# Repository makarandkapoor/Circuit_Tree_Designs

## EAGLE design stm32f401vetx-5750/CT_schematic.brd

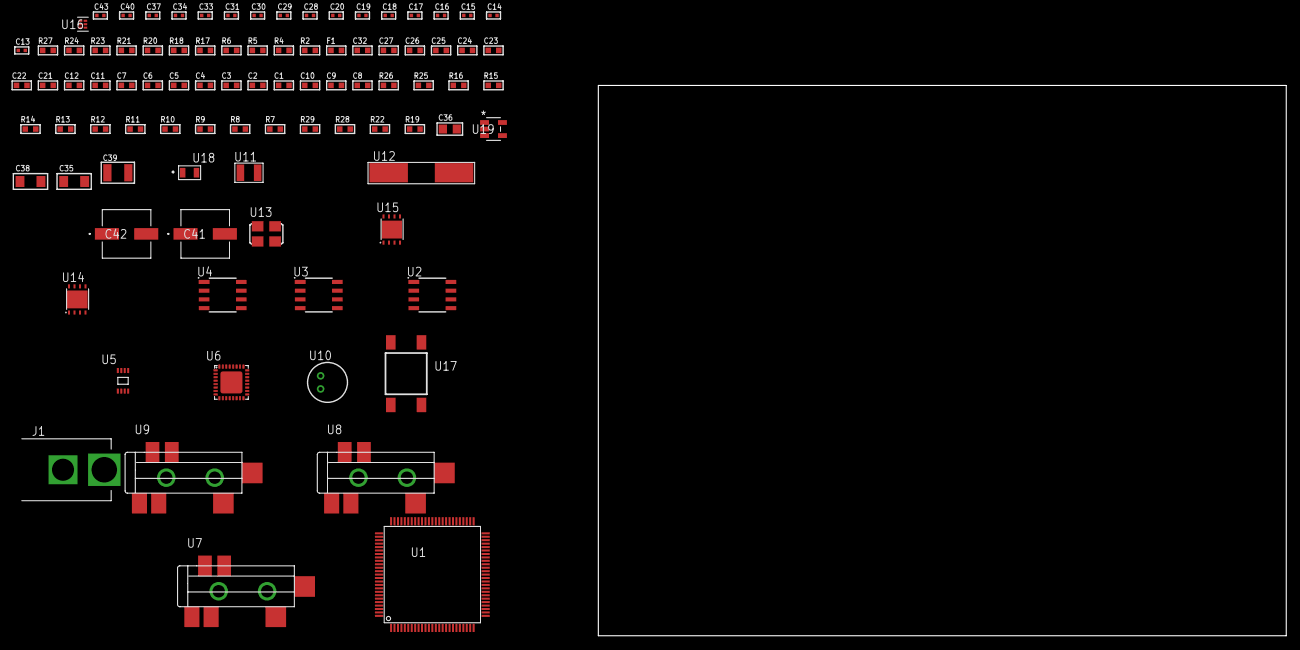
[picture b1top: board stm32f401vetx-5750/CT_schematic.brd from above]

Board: 2 copper layers, 100.0 x 80.0 mm, 91 parts (0 on the bottom side), 62 nets, no tracks yet.

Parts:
C1, C12, C21, C22, C23, C24, C25, C26, C27, C32: 1e-06; C0603
C2, C3, C4, C5, C6, C7: 1e-07; C0603
C8: 4.7e-06; C0603
C9, C10: 2.2e-06; C0603
C11: 1e-08; C0603
C13, C14, C15, C16: 1e-11; C0402
C17, C18, C19, C20, C33, C34, C37, C43: 1e-08; C0402
C28, C29, C30, C31, C40: 1e-07; C0402
C35, C38: 1e-05; C1206
C36: 1e-05; C0805
C39: 1e-05; C1210
C41, C42: 0.0001; EXV-9H
F1: 240.0; L0603
J1: PJ-037B; PJ-037B_PACKAGE
R2, R21, R24: 1000.0; R0603
R4: 4700.0; R0603
R5, R6: 2200.0; R0603
R7, R8, R9, R10, R11, R12, R13, R14, R15, R16, R25, R26: 10000.0; R0603
R17, R18: 1270.0; R0603
R19, R22: 100000.0; R0603
R20: 200.0; R0603
R23: 2231.0; R0603
R27: 9100.0; R0603
R28: 680000.0; R0603
R29: 120000.0; R0603
U1: STM32F401VET6; LQFP100
U2: AT25010B-SSHL-T; SOIC-8
U3: AT25128B-SSHL-T; SOIC-8
U4: AT25512N-SH-T; SOIC-8
U5: 24AA01T-I/MNY; TDFN-8/6MM
U6: SGTL5000XNAA3; QFN-32
U7, U8, U9: SJ-43515TS-SMT-TR
U10: WM-64PCT; WM-64PC
U11: ABS07-32.768KHZ-7-T
U12: ABLS-25.000MHZ-B2F-T
U13: ASFL-24.57MHZ-NCS; ASFL1
U14, U15: LP3878SDX-ADJ/NOPB; WSON-8
U16: TPS3895ADRYR; SON-6
U17: 4-1437565-2; SW_4-1437565-2
U18: Q65110A2395; LGM67K-G1J2-24-Z
U19: nc7sz125m5x; NC7SZ125M5X

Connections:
CLK_CRYSTAL_U1_8: C13.1, U1.8, U11.1
CLK_CRYSTAL_U1_9: C14.1, U1.9, U11.2
CLK_CRYSTAL_U1_12: C15.1, U1.12, U12.1
CLK_CRYSTAL_U1_13: C16.1, U1.13, U12.2
CLK_U6_21: U6.21, U13.3
GND: C1.2, C2.2, C3.2, C4.2, C5.2, C6.2, C7.2, C8.2, C9.2, C10.2, C11.2, C12.2, C13.2, C14.2, C15.2, C16.2, C17.2, C18.2, C19.2, C20.2, C28.2, C29.2, C30.2, C31.2, C32.2, C33.2, C34.2, C35.2, C36.2, C37.2, C38.2, C39.2, C40.2, C41.2, C42.2, C43.2, J1.2, R2.2, R7.2, R18.2, R21.2, R24.2, R27.2, R29.2, U1.10, U1.20, U1.27, U1.49, U1.74, U1.99, U2.4, U3.4, U4.4, U5.4, U5.7, U6.1, U6.3, U6.7, U6.EXP, U8.1, U9.1, U10.2, U13.2, U14.3, U14.PAD, U15.3, U15.PAD, U16.2, U18.C, U19.1, U19.3
NET_U1_14: R4.1, U1.14, U19.4
NET_U1_22: C11.1, C12.1, F1.1, U1.21, U1.22
NET_U1_48: C9.1, U1.48
NET_U1_73: C10.1, U1.73
NET_U1_92: R5.1, U1.92, U5.6
NET_U1_93: R6.1, U1.93, U5.5
NET_U1_94: R7.1, U1.94
NET_U1_98: U17.3, U17.4
NET_U2_3: R8.1, U2.3
NET_U2_7: R10.1, U2.7
NET_U3_3: R11.1, U3.3
NET_U3_7: R13.1, U3.7
NET_U4_3: R14.1, U4.3
NET_U4_7: R16.1, U4.7
NET_U6_10: C31.1, U6.10
NET_U6_29: R17.1, U6.29
NET_U6_31: R18.1, U6.31
NET_U7_1: U6.4, U7.1
NET_U7_2: U6.2, U7.2
NET_U7_5: U6.6, U7.5
NET_U8_2: C22.1, U8.2
NET_U8_5: C21.1, U8.5
NET_U9_2: C24.1, C25.1, U9.2
NET_U9_5: C23.1, U9.5
NET_U9_13: C24.2, C25.2
NET_U10_1: C26.1, C27.1, C32.1, U6.16, U10.1
NET_U10_15: C26.2, C27.2
NET_U14_1: C34.1, U14.1
NET_U14_6: R20.2, R21.1, U14.6
NET_U14_8: R19.1, U14.8
NET_U15_1: C37.1, U15.1
NET_U15_6: R23.2, R24.1, U15.6
NET_U15_8: R22.1, U15.8
NET_U16_1: R26.1, R27.1, U16.1
NET_U16_3: R28.2, R29.1, U16.3
NET_U16_4: R25.1, U16.4, U19.2
NET_U17_1: R2.1, U17.1, U17.2
PROC_I2S2_CK: U1.52, U6.24
PROC_I2S2_EXT_SD: U1.53, U6.25
PROC_I2S2_SD: U1.54, U6.26
PROC_I2S2_WS: U1.96, U6.23
PROC_SPI1_MISO: U1.31, U4.2
PROC_SPI1_MOSI: U1.32, U4.5
PROC_SPI1_NSS: R15.1, U1.29, U4.1
PROC_SPI1_SCK: U1.30, U4.6
PROC_SPI2_MISO: U1.17, U2.2
PROC_SPI2_MOSI: U1.18, U2.5
PROC_SPI2_NSS: R9.1, U1.51, U2.1
PROC_SPI2_SCK: U1.47, U2.6
PROC_SPI3_MISO: U1.79, U3.2
PROC_SPI3_MOSI: U1.80, U3.5
PROC_SPI3_NSS: R12.1, U1.77, U3.1
PROC_SPI3_SCK: U1.78, U3.6
VCC_S1_7V1: C35.1, C38.1, C41.1, C42.1, J1.1, R19.2, R22.2, U14.4, U15.4
VCC_TIER1_1V2: C28.1, C36.1, R20.1, U6.30, U14.5
VCC_TIER1_3V3: C1.1, C2.1, C3.1, C4.1, C5.1, C6.1, C7.1, C8.1, C17.1, C18.1, C19.1, C20.1, C29.1, C30.1, C33.1, C39.1, C40.1, C43.1, F1.2, R4.2, R5.2, R6.2, R8.2, R9.2, R10.2, R11.2, R12.2, R13.2, R14.2, R15.2, R16.2, R17.2, R23.1, R25.2, R26.2, R28.1, U1.6, U1.11, U1.19, U1.28, U1.50, U1.75, U1.100, U2.8, U3.8, U4.8, U5.8, U6.5, U6.20, U13.4, U15.5, U16.6, U19.5

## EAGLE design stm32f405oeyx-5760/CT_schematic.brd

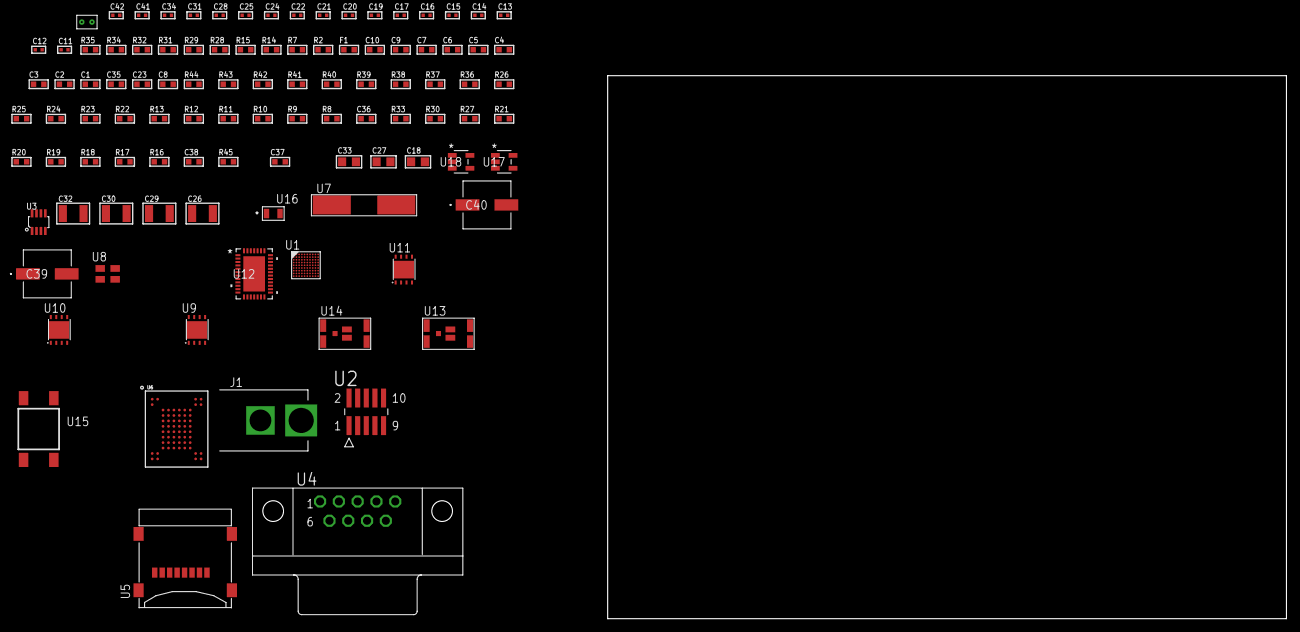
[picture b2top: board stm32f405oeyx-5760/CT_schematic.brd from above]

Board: 2 copper layers, 100.0 x 80.0 mm, 103 parts (0 on the bottom side), 71 nets, no tracks yet.

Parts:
C1, C10: 1e-06; C0603
C2, C3, C4, C5, C6, C7: 1e-07; C0603
C8: 4.7e-06; C0603
C9: 1e-08; C0603
C11, C12, C15, C16, C17, C19, C20, C21, C22, C34: 1e-07; C0402
C13, C14: 1e-11; C0402
C18, C27, C33: 1e-05; C0805
C23, C35: 2.2e-06; C0603
C24, C25, C28, C31, C41, C42: 1e-08; C0402
C26, C29, C30, C32: 1e-05; C1210
C36: 2.45e-08; R0603
C37: 2.8258362168397e-09; R0603
C38: 7.105e-09; R0603
C39, C40: 0.0001; EXV-9H
F1: 240.0; L0603
J1: PJ-037B; PJ-037B_PACKAGE
R2, R29, R32, R35: 1000.0; R0603
R7: 4700.0; R0603
R8, R9, R10, R11, R12, R13, R22, R23, R24, R25, R26, R36, R38, R39, R42, R43, R44: 10000.0; R0603
R14: 5.0; R0603
R15: 120.0; R0603
R16, R17, R18, R19, R20, R21, R27, R30, R33: 100000.0; R0603
R28, R34: 200.0; R0603
R31: 2231.0; R0603
R37: 75000.0; R0603
R40, R41: 95300.0; R0603
R45: 103345.45454545; R0603
U1: STM32F405OEY6; WLCSP90
U2: FTSH-105-01-L-DV-K; SAMTEC_FTSH-105-01-L-DV-K
U3: MAX3051EKA+T; SOT-23-8
U4: 182-009-113R531; 182-009-MALE
U5: 0472192001; MOLEX_47219-2001
U6: mt29f4g08abadah4; VFBGA-63
U7: ABLS-25.000MHZ-B2F-T
U8: ASEK-32.768KHz-ECST; ASEK
U9, U10, U11: LP3878SDX-ADJ/NOPB; WSON-8
U12: LTC2928CUHF#PBF; QFN-38_UHF
U13, U14: IRF8306MTRPbF; IRF8306MTRPBF
U15: 4-1437565-2; SW_4-1437565-2
U16: Q65110A2395; LGM67K-G1J2-24-Z
U17, U18: nc7sz125m5x; NC7SZ125M5X
U19: Dummy; DUMMY_PACKAGE_230

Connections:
CLK_CRYSTAL_U1_F9: C13.1, U1.F9, U7.1
CLK_CRYSTAL_U1_F10: C14.1, U1.F10, U7.2
CLK_U1_B10: U1.B10, U8.3
GND: C1.2, C2.2, C3.2, C4.2, C5.2, C6.2, C7.2, C8.2, C9.2, C10.2, C11.2, C12.2, C13.2, C14.2, C15.2, C16.2, C17.2, C18.2, C19.2, C20.2, C21.2, C22.2, C23.2, C24.2, C25.2, C26.2, C27.2, C28.2, C29.2, C30.2, C31.2, C32.2, C33.2, C34.2, C35.2, C36.2, C37.2, C38.2, C39.2, C40.2, C41.2, C42.2, J1.2, R2.2, R9.2, R14.2, R29.2, R32.2, R35.2, R37.2, R40.2, R41.2, R42.2, R43.2, R44.2, U1.C9, U1.E5, U1.E7, U1.E8, U1.H10, U2.3, U2.5, U3.2, U3.8, U4.5, U5.6, U5.G1, U5.G2, U5.G3, U5.G4, U6.C5, U6.F7, U6.K3, U6.K8, U8.2, U9.3, U9.PAD, U10.3, U10.PAD, U11.3, U11.PAD, U12.8, U12.9, U12.10, U12.12, U12.13, U12.24, U12.25, U12.30, U12.32, U12.39, U16.C, U17.2, U17.3, U18.1, U18.3, U19.1
NET_U1_A7: R9.1, U1.A7
NET_U1_A8: R8.1, U1.A8
NET_U1_B1: C12.1, U1.B1
NET_U1_D9: R10.1, U1.D9
NET_U1_G9: C9.1, C10.1, F1.1, U1.G9
NET_U1_G10: R7.1, U1.G10, U18.4
NET_U1_J10: U15.3, U15.4
NET_U2_9: R14.1, U2.9
NET_U3_6: R15.2, U3.6
NET_U4_2: R15.2, U3.6, U4.2
NET_U4_3: R15.1, U3.7, U4.3
NET_U6_C3: R26.1, U6.C3
NET_U9_1: C25.1, U9.1
NET_U9_6: R28.2, R29.1, U9.6
NET_U9_8: R27.1, U9.8
NET_U10_1: C28.1, U10.1
NET_U10_6: R31.2, R32.1, U10.6
NET_U10_8: R30.1, U10.8
NET_U11_1: C31.1, U11.1
NET_U11_6: R34.2, R35.1, U11.6
NET_U11_8: R33.1, U11.8
NET_U12_3: R43.1, U12.3
NET_U12_6: R40.1, U12.6
NET_U12_7: R41.1, U12.7
NET_U12_16: R42.1, R45.1, U12.16
NET_U12_18: R39.1, U12.18
NET_U12_19: R38.1, U12.19, U12.20
NET_U12_21: R36.1, R37.1, U12.21, U17.4, U18.2
NET_U12_22: C34.1, R36.2, R38.2, R39.2, U12.11, U12.22
NET_U12_26: C37.1, U12.26
NET_U12_27: C36.1, U12.27
NET_U12_28: C38.1, U12.28
NET_U12_38: R44.1, U12.38
NET_U13_3: U12.2, U13.3
NET_U14_3: U12.37, U14.3
NET_U15_1: R2.1, U15.1, U15.2
PROC_CAN1_RX: U1.C1, U3.4
PROC_CAN1_TX: U1.C2, U3.1
PROC_DAC_OUT2: U1.G8, U19.2
PROC_FSMC_D0: U1.F2, U6.H4
PROC_FSMC_D1: U1.F1, U6.J4
PROC_FSMC_D2: U1.D6, U6.K4
PROC_FSMC_D3: U1.C5, U6.K5
PROC_FSMC_D4: U1.G6, U6.K6
PROC_FSMC_D5: U1.H6, U6.J7
PROC_FSMC_D6: U1.J6, U6.K7
PROC_FSMC_D7: U1.F6, U6.J8
PROC_FSMC_NCE2: R23.1, U1.A5, U6.C6
PROC_FSMC_NOE: R25.1, U1.A4, U6.D4
PROC_FSMC_NWAIT: R22.1, U1.B5, U6.C8
PROC_FSMC_NWE: R24.1, U1.C6, U6.C7
PROC_SDIO_CK: R17.1, U1.A3, U5.5
PROC_SDIO_CMD: R16.1, U1.B4, U5.3
PROC_SDIO_D0: R18.1, U1.E2, U5.7
PROC_SDIO_D1: R19.1, U1.E3, U5.8
PROC_SDIO_D2: R20.1, U1.D5, U5.1
PROC_SDIO_D3: R21.1, U1.C4, U5.2
PROC_SYS_JTCK_SWCLK: R12.1, U1.A2, U2.4
PROC_SYS_JTDO_SWO: U1.B6, U2.6
PROC_SYS_JTMS_SWDIO: R13.1, U1.D4, U2.2
RST_OUT_U2_JTAG_RST_B: R11.1, U2.10, U17.1
VCC_12V7: C35.1, C39.1, C40.1, J1.1, R45.2, U12.23, U13.1, U13.2, U13.6, U13.7, U14.1, U14.2, U14.6, U14.7
VCC_S1_12V7: C26.1, C29.1, R27.2, R30.2, U9.4, U10.4, U13.4, U13.5
VCC_S2_12V7: C32.1, R33.2, U11.4, U14.4, U14.5
VCC_TIER1_1V2: C11.1, C27.1, R28.1, U1.F4, U9.5
VCC_TIER1_3V3: C1.1, C2.1, C3.1, C4.1, C5.1, C6.1, C7.1, C8.1, C15.1, C16.1, C17.1, C18.1, C19.1, C20.1, C21.1, C22.1, C23.1, C24.1, C30.1, C41.1, C42.1, F1.2, R7.2, R8.2, R10.2, R11.2, R12.2, R13.2, R16.2, R17.2, R18.2, R19.2, R20.2, R21.2, R22.2, R23.2, R24.2, R25.2, R26.2, R31.1, U1.A1, U1.A10, U1.B8, U1.E4, U1.E6, U1.F7, U2.1, U3.3, U5.4, U6.D3, U6.G4, U6.H8, U6.J6, U8.4, U10.5, U17.5, U18.5
VCC_TIER2_1V2: C33.1, R34.1, U11.5

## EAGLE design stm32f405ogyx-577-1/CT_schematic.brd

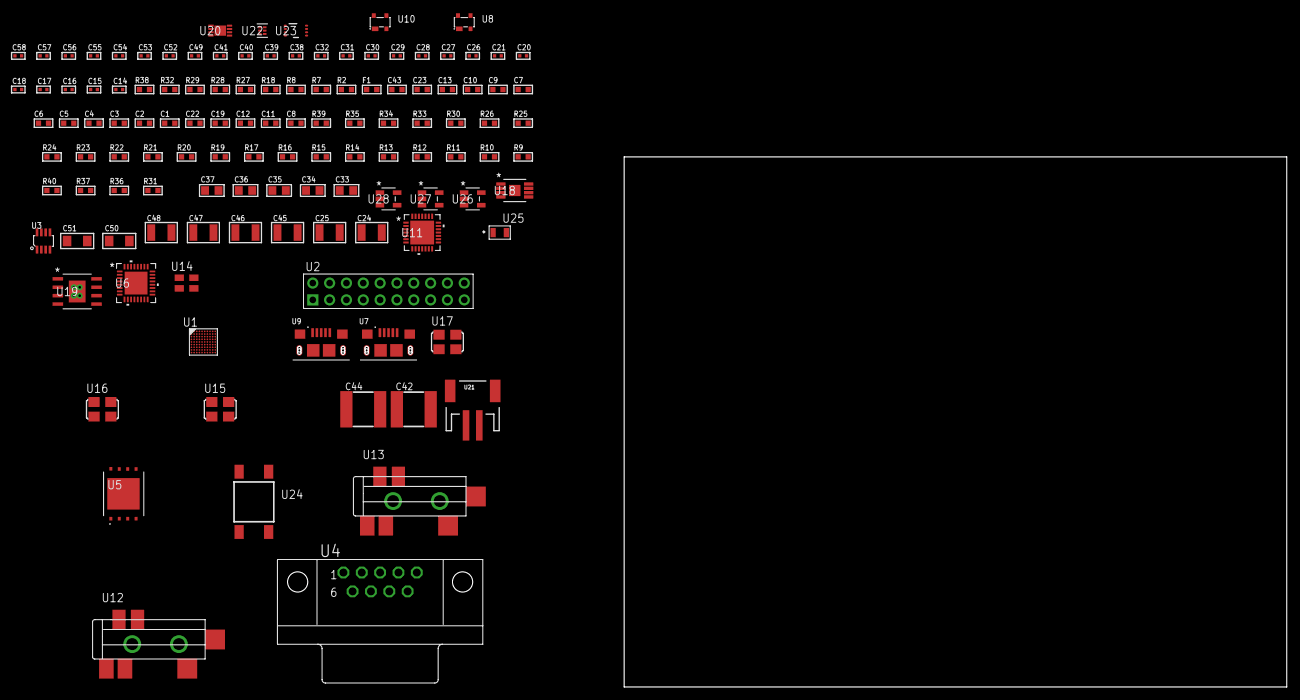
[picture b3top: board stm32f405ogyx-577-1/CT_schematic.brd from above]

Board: 2 copper layers, 122 parts (0 on the bottom side), 74 nets, no tracks yet.

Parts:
C1, C10, C13, C23, C43: 1e-06; C0603
C2, C3, C4, C5, C6, C7: 1e-07; C0603
C8: 4.7e-06; C0603
C9: 1e-08; C0603
C11, C12, C19, C22: 2.2e-06; C0603
C14, C15, C16, C18, C20, C21, C28, C29, C30, C31, C32, C49, C53, C55: 1e-07; C0402
C17, C38, C39, C40, C41, C52, C54, C56, C57, C58: 1e-08; C0402
C24, C25: 2.2e-05; C1210
C26, C27: 1e-09; C0402
C33, C34, C35, C36, C37: 1e-05; C0805
C42, C44: 6.8e-05; 2220
C45, C46, C47, C48: 1e-05; C1210
C50, C51: 1e-05; C1206
F1: 240.0; L0603
R2: 1000.0; R0603
R7, R8: 4700.0; R0603
R9, R10, R11, R12, R13, R14, R15, R16, R17, R19, R20, R21, R22, R23, R30, R33, R34, R39: 10000.0; R0603
R18: 120.0; R0603
R24, R25, R26: 47000.0; R0603
R27: 680.0; R0603
R28: 3900.0; R0603
R29, R32: 2200.0; R0603
R31: 4031.5447154472; R0603
R35: 82000.0; R0603
R36: 300000.0; R0603
R37: 120000.0; R0603
R38: 2000.0; R0603
R40: 200000.0; R0603
U1: STM32F405OGY6; WLCSP90
U2: TST-110-05-T-D-RA
U3: MAX3051EKA+T; SOT-23-8
U4: 182-009-113R531; 182-009-MALE
U5: S25FL128SDPNFI001; WNG008
U6: TUSB1210BRHBR; RHB32_3P45X3P45
U7, U9: 10118193-0001LF; FCI_10118193-0001LF
U8, U10: prtr5v0u2ax; SOT143B
U11: WM8731CLSEFL; QFN-28
U12, U13: SJ-43515TS-SMT-TR
U14: ASEK-32.768KHz-ECST; ASEK
U15: ASFL1-12.288MHZ-EC-T; ASFL1
U16: ASFL1-19.2MHZ-NCS; ASFL1
U17: ASFL1-25MHZ-NCS; ASFL1
U18: MIC47100YMME; MSOP-8_EP
U19: MIC5234YME; SOIC-8_EP
U20: MCP73831T-2ACI/MC; DFN8_2X3MC
U21: S2B-PH-SM4-TB(LF)(SN); JST-2-SMD
U22: TPS3895ADRYR; SON-6
U23: LSF0102DCTR; DCU0008A_N
U24: 4-1437565-2; SW_4-1437565-2
U25: Q65110A2395; LGM67K-G1J2-24-Z
U26, U27, U28: nc7sz125m5x; NC7SZ125M5X

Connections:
CLK_U1_B10: U1.B10, U14.3
CLK_U1_F10: U1.F10, U17.3
CLK_U6_1: U6.1, U16.3
CLK_U11_1: U11.1, U15.3
GND: C1.2, C2.2, C3.2, C4.2, C5.2, C6.2, C7.2, C8.2, C9.2, C10.2, C11.2, C12.2, C13.2, C14.2, C15.2, C16.2, C17.2, C18.2, C19.2, C20.2, C21.2, C22.2, C23.2, C27.2, C28.2, C29.2, C30.2, C31.2, C32.2, C33.2, C34.2, C35.2, C36.2, C37.2, C38.2, C39.2, C40.2, C41.2, C42.2, C43.2, C44.2, C45.2, C46.2, C47.2, C48.2, C49.2, C50.2, C51.2, C52.2, C53.2, C54.2, C55.2, C56.2, C57.2, C58.2, R2.2, R10.2, R11.2, R17.2, R23.2, R24.2, R25.2, R26.2, R29.2, R32.2, R35.2, R37.2, R38.2, U1.C1, U1.C9, U1.E5, U1.E7, U1.E8, U1.H10, U2.4, U2.6, U2.8, U2.10, U2.12, U2.14, U2.16, U2.18, U2.20, U3.2, U3.8, U4.5, U5.4, U5.PAD, U6.33, U7.5, U7.6, U7.7, U7.8, U7.9, U8.1, U9.5, U9.6, U9.7, U9.8, U9.9, U10.1, U11.4, U11.15, U11.19, U11.25, U11.26, U11.29, U12.1, U13.1, U14.2, U15.2, U16.2, U17.2, U18.3, U18.EPAD, U19.7, U19.EPAD, U20.6, U20.9, U21.2, U22.2, U23.1, U25.C, U26.2, U26.3, U27.1, U27.3, U28.1, U28.3
INPUT_USBPOWER_5V: C23.1, C50.1, R39.2, U6.22, U7.1, U8.4, U20.1, U20.2
NET_U1_A7: R10.1, U1.A7
NET_U1_A8: R9.1, U1.A8
NET_U1_B1: C12.1, U1.B1
NET_U1_D9: R11.1, U1.D9
NET_U1_F4: C11.1, U1.F4
NET_U1_G9: C9.1, C10.1, F1.1, U1.G9
NET_U1_G10: R7.1, U1.G10, U27.4
NET_U1_J10: U24.3, U24.4
NET_U2_19: R17.1, U2.19
NET_U3_6: R18.2, U3.6
NET_U4_2: R18.2, U3.6, U4.2
NET_U4_3: R18.1, U3.7, U4.3
NET_U5_3: R19.1, U5.3
NET_U5_7: R21.1, U5.7
NET_U6_11: R22.1, U6.11
NET_U6_12: C22.1, U6.12
NET_U6_14: R23.1, U6.14
NET_U6_20: C19.1, U6.20
NET_U6_27: R8.1, U6.27, U28.4
NET_U7_2: U6.19, U7.2, U8.3
NET_U7_3: U6.18, U7.3, U8.2
NET_U11_20: C32.1, C37.1, U11.20
NET_U12_2: C25.1, R25.1, U12.2
NET_U12_5: C24.1, R24.1, U12.5
NET_U13_5: C26.1, C27.1, R26.1, R27.1, U13.5
NET_U18_6: R28.2, R29.1, U18.6
NET_U19_4: R31.2, R32.1, U19.4
NET_U20_5: R39.1, U20.5
NET_U20_8: R38.1, U20.8
NET_U22_1: R34.1, R35.1, U22.1
NET_U22_3: R36.2, R37.1, U22.3
NET_U22_4: R33.1, U22.4, U26.4, U27.2, U28.2
NET_U23_8: R40.1, U23.8
NET_U24_1: R2.1, U24.1, U24.2
PROC_CAN1_RX_TOXCVR: U3.4, U23.5
PROC_CAN1_TX_TOXCVR: U3.1, U23.6
PROC_I2S3_CK: U1.D5, U11.7
PROC_I2S3_EXT_SD: U1.C4, U11.10
PROC_I2S3_SD: U1.A3, U11.8
PROC_I2S3_WS: U1.J9, U11.9, U11.11
PROC_SPI2_MISO: U1.J2, U5.2
PROC_SPI2_MOSI: U1.H1, U5.5
PROC_SPI2_NSS: R20.1, U1.C3, U5.1
PROC_SPI2_SCK: U1.B2, U5.6
PROC_SYS_JTCK_SWCLK: R15.1, U1.A2, U2.9
PROC_SYS_JTDI: R13.1, U1.B3, U2.5
PROC_SYS_JTDO_SWO: U1.B6, U2.13
PROC_SYS_JTMS_SWDIO: R14.1, U1.D4, U2.7
PROC_SYS_JTRST: R12.1, U1.A6, U2.3
PROC_USB_OTG_FS_DM: U1.C1, U9.2, U10.3
PROC_USB_OTG_FS_DP: U1.C2, U9.3, U10.2
PROC_USB_OTG_FS_VBUS: C13.1, U1.D2, U9.1, U10.4
PROC_USB_OTG_HS_ULPI_CK: U1.G8, U6.26
PROC_USB_OTG_HS_ULPI_D0: U1.H9, U6.3
PROC_USB_OTG_HS_ULPI_D1: U1.G7, U6.4
PROC_USB_OTG_HS_ULPI_D2: U1.H7, U6.5
PROC_USB_OTG_HS_ULPI_D3: U1.H4, U6.6
PROC_USB_OTG_HS_ULPI_D4: U1.J4, U6.7
PROC_USB_OTG_HS_ULPI_D5: U1.J3, U6.9
PROC_USB_OTG_HS_ULPI_D6: U1.J1, U6.10
PROC_USB_OTG_HS_ULPI_D7: U1.D7, U6.13
PROC_USB_OTG_HS_ULPI_DIR: U1.D10, U6.31
PROC_USB_OTG_HS_ULPI_NXT: U1.E9, U6.2
PROC_USB_OTG_HS_ULPI_STP: U1.E10, U6.29
RST_OUT_U2_SRESET_B: R16.1, U2.15, U26.1
VCC_S1_3V7: C42.1, C43.1, C45.1, C46.1, C51.1, R30.1, R30.2, U18.1, U18.2, U18.4, U18.5, U19.5, U19.8, U20.3, U20.4, U21.1
VCC_TIER1_1V8: C1.1, C2.1, C3.1, C4.1, C5.1, C6.1, C7.1, C8.1, C15.1, C17.1, C20.1, C21.1, C28.1, C29.1, C30.1, C31.1, C33.1, C34.1, C35.1, C36.1, C44.1, C49.1, C54.1, C55.1, C56.1, C57.1, C58.1, F1.2, R7.2, R8.2, R9.2, R12.2, R13.2, R14.2, R15.2, R16.2, R19.2, R20.2, R21.2, R22.2, R28.1, R33.2, R34.2, R36.1, U1.A1, U1.A10, U1.B8, U1.E4, U1.E6, U1.F7, U2.1, U5.8, U6.28, U6.30, U6.32, U11.3, U11.5, U11.12, U11.18, U18.7, U18.8, U22.6, U23.2, U26.5, U27.5, U28.5
VCC_TIER1_3V3: C14.1, C16.1, C18.1, C38.1, C39.1, C40.1, C41.1, C47.1, C48.1, C52.1, C53.1, R31.1, R40.2, U2.2, U3.3, U6.21, U14.4, U15.4, U16.4, U17.4, U19.1, U23.7

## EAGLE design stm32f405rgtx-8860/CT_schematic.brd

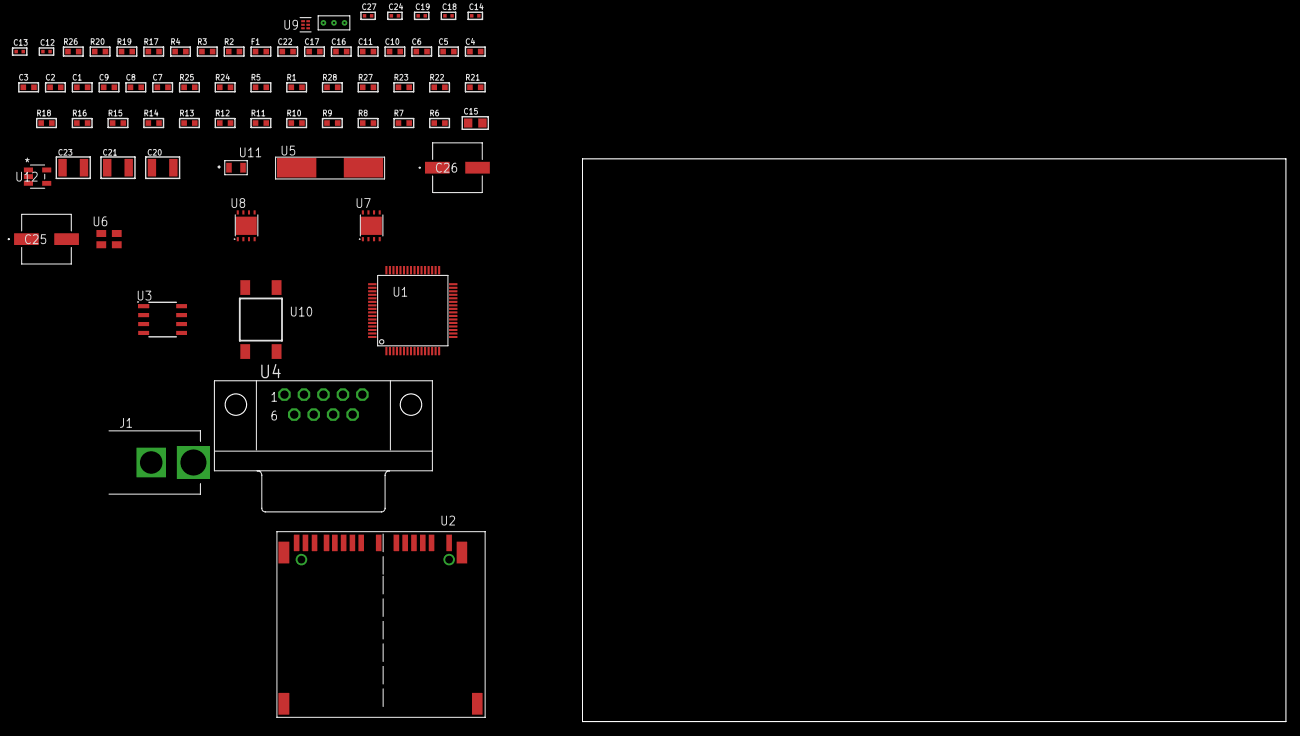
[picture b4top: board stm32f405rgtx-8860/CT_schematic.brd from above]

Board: 2 copper layers, 100.0 x 80.0 mm, 70 parts (0 on the bottom side), 42 nets, no tracks yet.

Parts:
C1, C11, C16, C17: 1e-06; C0603
C2, C3, C4, C5, C6: 1e-07; C0603
C7: 4.7e-06; C0603
C8, C9: 2.2e-06; C0603
C10: 1e-08; C0603
C12, C13: 1e-11; C0402
C14, C24: 1e-07; C0402
C15: 1e-05; C0805
C18, C19, C27: 1e-08; C0402
C20, C21, C23: 1e-05; C1210
C22: 8e-07; R0603
C25, C26: 0.0001; EXV-9H
F1: 240.0; L0603
J1: PJ-037B; PJ-037B_PACKAGE
R1, R5, R24, R25: 10000.0; R0603
R2, R20: 1000.0; R0603
R3: 1600.5; R0603
R4: 4700.0; R0603
R6, R7, R8, R9, R10, R11, R12, R13, R14, R15, R16, R18, R21, R23: 100000.0; R0603
R17: 120.0; R0603
R19: 2231.0; R0603
R22: 300000.0; R0603
R26: 9100.0; R0603
R27: 680000.0; R0603
R28: 120000.0; R0603
U1: stm32f405RGT7; LQFP64
U2: 10100565
U3: MCP2562-E/SN; SOIC-8
U4: 182-009-113R531; 182-009-MALE
U5: ABLS-25.000MHZ-B2F-T
U6: ASEK-32.768KHz-ECST; ASEK
U7: LP3878SDX-ADJ/NOPB; WSON-8
U8: LP2951ACSDX/NOPB; WSON-8
U9: TPS3895ADRYR; SON-6
U10: 4-1437565-2; SW_4-1437565-2
U11: Q65110A2395; LGM67K-G1J2-24-Z
U12: nc7sz125m5x; NC7SZ125M5X
U13: Dummy; DUMMY_PACKAGE_149

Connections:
CLK_CRYSTAL_U1_5: C12.1, U1.5, U5.1
CLK_CRYSTAL_U1_6: C13.1, U1.6, U5.2
CLK_U1_3: U1.3, U6.3
GND: C1.2, C2.2, C3.2, C4.2, C5.2, C6.2, C7.2, C8.2, C9.2, C10.2, C11.2, C12.2, C13.2, C14.2, C15.2, C16.2, C17.2, C18.2, C19.2, C20.2, C21.2, C22.2, C23.2, C24.2, C25.2, C26.2, C27.2, J1.2, R2.2, R5.2, R20.2, R23.2, R26.2, R28.2, U1.12, U1.18, U1.63, U2.6, U2.10, U2.12, U2.16, U2.17, U2.20, U2.21, U3.2, U3.8, U4.5, U6.2, U7.3, U7.PAD, U8.3, U8.4, U8.PAD, U9.2, U11.C, U12.1, U12.3, U13.1
NET_U1_7: R4.1, U1.7, U12.4
NET_U1_13: C10.1, C11.1, F1.1, U1.13
NET_U1_31: C8.1, U1.31
NET_U1_47: C9.1, U1.47
NET_U1_58: R3.1, U1.58, U11.A
NET_U1_59: R1.1, U1.59, U10.3, U10.4
NET_U1_60: R5.1, U1.60
NET_U2_1: R8.1, U2.1
NET_U2_2: R7.1, U2.2
NET_U2_18: U2.18, U2.19
NET_U3_6: R17.2, U3.6
NET_U4_2: R17.2, U3.6, U4.2
NET_U4_3: R17.1, U3.7, U4.3
NET_U7_1: C19.1, U7.1
NET_U7_6: R19.2, R20.1, U7.6
NET_U7_8: R18.1, U7.8
NET_U8_5: R21.1, U8.5
NET_U8_7: R22.2, R23.1, U8.7
NET_U9_1: R25.1, R26.1, U9.1
NET_U9_3: R27.2, R28.1, U9.3
NET_U9_4: R24.1, U9.4, U12.2
NET_U10_1: R2.1, U10.1, U10.2
PROC_CAN1_RX: U1.44, U3.4
PROC_CAN1_TX: U1.45, U3.1
PROC_SDIO_CK: R6.1, U1.53, U2.8
PROC_SDIO_D0: R9.1, U1.39, U2.4
PROC_SDIO_D1: R10.1, U1.40, U2.3
PROC_SDIO_D2: R11.1, U1.51, U2.15
PROC_SDIO_D3: R12.1, U1.52, U2.14
PROC_SDIO_D4: R13.1, U1.61, U2.13
PROC_SDIO_D5: R14.1, U1.62, U2.11
PROC_SDIO_D6: R15.1, U1.37, U2.7
PROC_SDIO_D7: R16.1, U1.38, U2.5
PROC_TIM1_CH2: U1.42, U13.2
PROC_TIM1_CH2N: U1.26, U13.3
VCC_S1_15V9: C20.1, C22.1, C25.1, C26.1, J1.1, R18.2, U7.4, U8.8
VCC_TIER1_3V3: C1.1, C2.1, C3.1, C4.1, C5.1, C6.1, C7.1, C14.1, C15.1, C17.1, C18.1, C21.1, C24.1, C27.1, F1.2, R1.2, R3.2, R4.2, R6.2, R7.2, R8.2, R9.2, R10.2, R11.2, R12.2, R13.2, R14.2, R15.2, R16.2, R19.1, R24.2, R25.2, R27.1, U1.1, U1.19, U1.32, U1.48, U1.64, U2.9, U3.5, U6.4, U7.5, U9.6, U12.5
VCC_TIER1_5V0: C16.1, C23.1, R21.2, R22.1, U3.3, U8.1

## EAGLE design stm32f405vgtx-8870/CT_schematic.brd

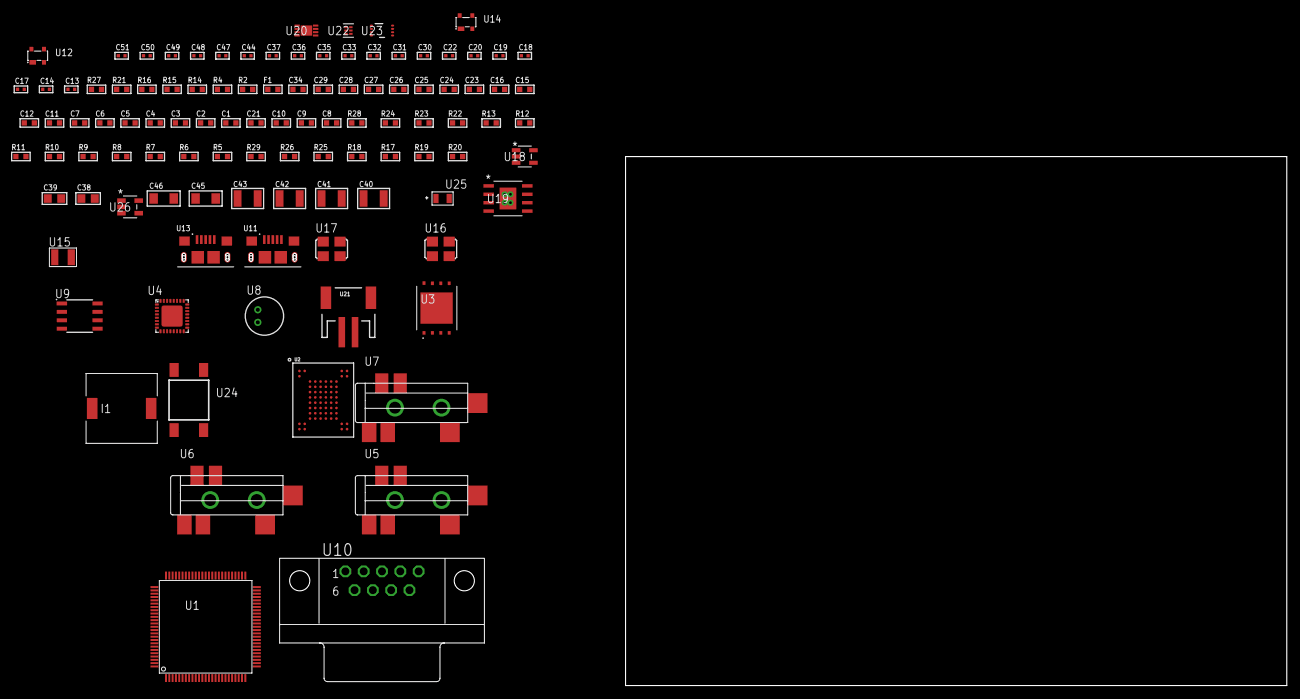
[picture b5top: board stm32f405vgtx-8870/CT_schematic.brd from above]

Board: 2 copper layers, 106 parts (0 on the bottom side), 73 nets, no tracks yet.

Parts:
C1, C12, C15, C16, C23, C24, C25, C26, C27, C28, C29, C34: 1e-06; C0603
C2, C3, C4, C5, C6, C7: 1e-07; C0603
C8: 4.7e-06; C0603
C9, C10, C21: 2.2e-06; C0603
C11: 1e-08; C0603
C13, C14: 1e-11; C0402
C17, C18, C19, C20, C30, C31, C32, C33, C35, C44, C48, C50: 1e-07; C0402
C22, C36, C37, C47, C49, C51: 1e-08; C0402
C38, C39: 1e-05; C0805
C40, C41, C42, C43: 1e-05; C1210
C45, C46: 1e-05; C1206
F1: 240.0; L0603
I1: 3.8e-06; DR1040
R2: 1000.0; R0603
R4: 4700.0; R0603
R5, R6, R7, R8, R9, R10, R11, R12, R13, R22, R23, R28: 10000.0; R0603
R14, R15: 1270.0; R0603
R16: 120.0; R0603
R17: 100000.0; R0603
R18: 490000.0; R0603
R19: 1000000.0; R0603
R20: 4031.5447154472; R0603
R21: 2200.0; R0603
R24: 82000.0; R0603
R25: 300000.0; R0603
R26: 120000.0; R0603
R27: 2000.0; R0603
R29: 200000.0; R0603
U1: stm32f405VGT7; LQFP100
U2: mt29f4g08abbdah4; VFBGA-63
U3: S25FL128SDPNFI001; WNG008
U4: SGTL5000XNAA3; QFN-32
U5, U6, U7: SJ-43515TS-SMT-TR
U8: WM-64PCT; WM-64PC
U9: SN65HVD230D; SOIC-8
U10: 182-009-113R531; 182-009-MALE
U11, U13: 10118193-0001LF; FCI_10118193-0001LF
U12, U14: prtr5v0u2ax; SOT143B
U15: ABS07-32.768KHZ-7-T
U16: ASFL-24.57MHZ-NCS; ASFL1
U17: ASFL1-25MHZ-NCS; ASFL1
U18: ltc3406es5; TSOT-23-5
U19: MIC5234YME; SOIC-8_EP
U20: MCP73831T-2ACI/MC; DFN8_2X3MC
U21: S2B-PH-SM4-TB(LF)(SN); JST-2-SMD
U22: TPS3895ADRYR; SON-6
U23: LSF0102DCTR; DCU0008A_N
U24: 4-1437565-2; SW_4-1437565-2
U25: Q65110A2395; LGM67K-G1J2-24-Z
U26: nc7sz125m5x; NC7SZ125M5X

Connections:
CLK_CRYSTAL_U1_8: C13.1, U1.8, U15.1
CLK_CRYSTAL_U1_9: C14.1, U1.9, U15.2
CLK_U1_12: U1.12, U17.3
CLK_U4_21: U4.21, U16.3
GND: C1.2, C2.2, C3.2, C4.2, C5.2, C6.2, C7.2, C8.2, C9.2, C10.2, C11.2, C12.2, C13.2, C14.2, C15.2, C16.2, C17.2, C18.2, C19.2, C20.2, C21.2, C22.2, C30.2, C31.2, C32.2, C33.2, C34.2, C35.2, C36.2, C37.2, C38.2, C39.1, C39.2, C40.2, C41.2, C42.2, C43.2, C44.2, C45.2, C46.2, C47.2, C48.2, C49.2, C50.2, C51.2, R2.2, R5.2, R15.2, R17.2, R18.2, R21.2, R24.2, R26.2, R27.2, U1.10, U1.20, U1.27, U1.52, U1.70, U1.74, U1.99, U2.C5, U2.F7, U2.K3, U2.K8, U3.4, U3.PAD, U4.1, U4.3, U4.7, U4.EXP, U6.1, U7.1, U8.2, U9.2, U10.5, U11.5, U11.6, U11.7, U11.8, U11.9, U12.1, U13.5, U13.6, U13.7, U13.8, U13.9, U14.1, U16.2, U17.2, U18.2, U19.7, U19.EPAD, U20.6, U20.9, U21.2, U22.2, U23.1, U25.C, U26.1, U26.3
INPUT_USBPOWER_5V: C16.1, C45.1, R28.2, U1.52, U11.1, U12.4, U20.1, U20.2
NET_U1_14: R4.1, U1.14, U26.4
NET_U1_22: C11.1, C12.1, F1.1, U1.21, U1.22
NET_U1_49: C9.1, U1.49
NET_U1_73: C10.1, U1.73
NET_U1_94: R5.1, U1.94
NET_U1_98: U24.3, U24.4
NET_U2_C3: R10.1, U2.C3
NET_U3_3: R11.1, U3.3
NET_U3_7: R13.1, U3.7
NET_U4_10: C33.1, U4.10
NET_U4_29: R14.1, U4.29
NET_U4_31: R15.1, U4.31
NET_U5_1: U4.4, U5.1
NET_U5_2: U4.2, U5.2
NET_U5_5: U4.6, U5.5
NET_U6_2: C24.1, U6.2
NET_U6_5: C23.1, U6.5
NET_U7_2: C26.1, C27.1, U7.2
NET_U7_5: C25.1, U7.5
NET_U7_13: C26.2, C27.2
NET_U8_1: C28.1, C29.1, C34.1, U4.16, U8.1
NET_U8_15: C28.2, C29.2
NET_U9_6: R16.2, U9.6
NET_U9_8: R17.1, U9.8
NET_U10_2: R16.2, U9.6, U10.2
NET_U10_3: R16.1, U9.7, U10.3
NET_U18_3: I1.1, U18.3
NET_U18_5: R18.1, R19.1, U18.5
NET_U18_ATNET_3: I1.2, R19.2
NET_U19_4: R20.2, R21.1, U19.4
NET_U20_5: R28.1, U20.5
NET_U20_8: R27.1, U20.8
NET_U22_1: R23.1, R24.1, U22.1
NET_U22_3: R25.2, R26.1, U22.3
NET_U22_4: R22.1, U22.4, U26.2
NET_U23_8: R29.1, U23.8
NET_U24_1: R2.1, U24.1, U24.2
PROC_CAN1_RX_TOXCVR: U9.4, U23.5
PROC_CAN1_TX_TOXCVR: U9.1, U23.6
PROC_FSMC_D0: U1.61, U2.H4
PROC_FSMC_D1: U1.62, U2.J4
PROC_FSMC_D2: U1.81, U2.K4
PROC_FSMC_D3: U1.82, U2.K5
PROC_FSMC_D4: U1.38, U2.K6
PROC_FSMC_D5: U1.39, U2.J7
PROC_FSMC_D6: U1.40, U2.K7
PROC_FSMC_D7: U1.41, U2.J8
PROC_FSMC_NCE2: R7.1, U1.88, U2.C6
PROC_FSMC_NOE: R9.1, U1.85, U2.D4
PROC_FSMC_NWAIT: R6.1, U1.87, U2.C8
PROC_FSMC_NWE: R8.1, U1.86, U2.C7
PROC_I2S2_CK: U1.47, U4.24
PROC_I2S2_EXT_SD: U1.17, U4.25
PROC_I2S2_SD: U1.18, U4.26
PROC_I2S2_WS: U1.51, U4.23
PROC_SPI1_MISO: U1.31, U3.2
PROC_SPI1_MOSI: U1.32, U3.5
PROC_SPI1_NSS: R12.1, U1.29, U3.1
PROC_SPI1_SCK: U1.30, U3.6
PROC_USB_OTG_FS_DM: U1.70, U13.2, U14.3
PROC_USB_OTG_FS_DP: U1.71, U13.3, U14.2
PROC_USB_OTG_FS_VBUS: C15.1, U1.68, U13.1, U14.4
PROC_USB_OTG_HS_DM: U1.53, U11.2, U12.3
PROC_USB_OTG_HS_DP: U1.54, U11.3, U12.2
VCC_S1_3V7: C38.1, C40.1, C41.1, C46.1, U18.4, U19.5, U19.8, U20.3, U20.4, U21.1
VCC_TIER1_1V8: C1.1, C2.1, C3.1, C4.1, C5.1, C6.1, C7.1, C8.1, C17.1, C18.1, C19.1, C20.1, C21.1, C22.1, C30.1, C31.1, C32.1, C39.2, C44.1, C49.1, C50.1, C51.1, F1.2, I1.2, R4.2, R6.2, R7.2, R8.2, R9.2, R10.2, R11.2, R12.2, R13.2, R14.2, R19.2, R22.2, R23.2, R25.1, U1.6, U1.11, U1.19, U1.28, U1.50, U1.75, U1.100, U2.D3, U2.G4, U2.H8, U2.J6, U3.8, U4.5, U4.20, U4.30, U22.6, U23.2, U26.5
VCC_TIER1_3V3: C35.1, C36.1, C37.1, C42.1, C43.1, C47.1, C48.1, R20.1, R29.2, U9.3, U16.4, U17.4, U19.1, U23.7

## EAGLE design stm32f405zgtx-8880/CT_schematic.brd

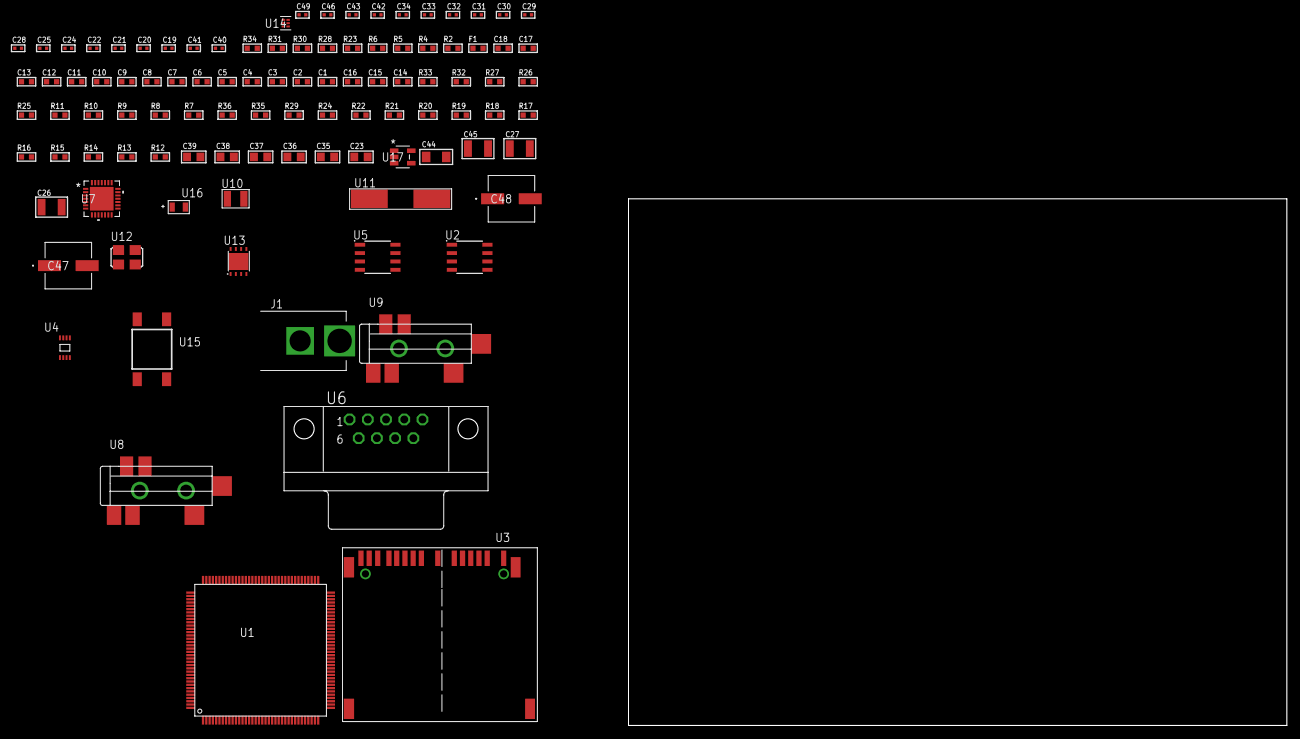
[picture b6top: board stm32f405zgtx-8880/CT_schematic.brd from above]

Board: 2 copper layers, 100.0 x 80.0 mm, 102 parts (0 on the bottom side), 56 nets, no tracks yet.

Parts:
C1, C18: 1e-06; C0603
C2, C3, C4, C5, C6, C7, C8, C9, C10, C11, C12, C13: 1e-07; C0603
C14: 4.7e-06; C0603
C15, C16: 2.2e-06; C0603
C17: 1e-08; C0603
C19, C20: 1e-11; C0402
C21, C24, C42, C43, C49: 1e-08; C0402
C22, C25, C30, C31, C32, C33, C34, C46: 1e-07; C0402
C23, C35, C36, C37, C38, C39: 1e-05; C0805
C26, C27: 2.2e-05; C1210
C28, C29: 1e-09; C0402
C40, C41: 2.2e-11; C0402
C44: 1e-05; C1206
C45: 1e-05; C1210
C47, C48: 0.0001; EXV-9H
F1: 240.0; L0603
J1: PJ-037B; PJ-037B_PACKAGE
R2, R31: 1000.0; R0603
R4: 4700.0; R0603
R5, R6: 2200.0; R0603
R7, R8, R9, R10, R11, R32, R33: 10000.0; R0603
R12, R13, R14, R15, R16, R17, R18, R19, R20, R21, R22, R29: 100000.0; R0603
R23: 120.0; R0603
R24: 470000.0; R0603
R25, R26, R27: 47000.0; R0603
R28: 680.0; R0603
R30: 2231.0; R0603
R34: 9100.0; R0603
R35: 680000.0; R0603
R36: 120000.0; R0603
U1: stm32f405ZGT6; LQFP144
U2: AT25020B-SSHL-T; SOIC-8
U3: 10100565
U4: 24AA16-I/MC; TDFN-8/6MM
U5: SN65HVD230D; SOIC-8
U6: 182-009-113R531; 182-009-MALE
U7: WM8731CLSEFL; QFN-28
U8, U9: SJ-43515TS-SMT-TR
U10: ABS07-32.768KHZ-7-T
U11: ABLS-12.288MHZ-B4-T
U12: ASFL1-25MHZ-NCS; ASFL1
U13: LP3878SDX-ADJ/NOPB; WSON-8
U14: TPS3895ADRYR; SON-6
U15: 4-1437565-2; SW_4-1437565-2
U16: Q65110A2395; LGM67K-G1J2-24-Z
U17: nc7sz125m5x; NC7SZ125M5X

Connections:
CLK_CRYSTAL_U1_8: C19.1, U1.8, U10.1
CLK_CRYSTAL_U1_9: C20.1, U1.9, U10.2
CLK_CRYSTAL_U7_1: C40.1, U7.1, U11.1
CLK_CRYSTAL_U7_2: C41.1, U7.2, U11.2
CLK_U1_23: U1.23, U12.3
GND: C1.2, C2.2, C3.2, C4.2, C5.2, C6.2, C7.2, C8.2, C9.2, C10.2, C11.2, C12.2, C13.2, C14.2, C15.2, C16.2, C17.2, C18.2, C19.2, C20.2, C21.2, C22.2, C23.2, C24.2, C25.2, C29.2, C30.2, C31.2, C32.2, C33.2, C34.2, C35.2, C36.2, C37.2, C38.2, C39.2, C40.2, C41.2, C42.2, C43.2, C44.2, C45.2, C46.2, C47.2, C48.2, C49.2, J1.2, R2.2, R8.2, R24.2, R25.2, R26.2, R27.2, R31.2, R34.2, R36.2, U1.16, U1.31, U1.38, U1.51, U1.61, U1.83, U1.94, U1.107, U1.120, U1.130, U2.4, U3.6, U3.10, U3.12, U3.16, U3.17, U3.20, U3.21, U4.4, U5.2, U6.5, U7.4, U7.15, U7.19, U7.25, U7.26, U7.29, U8.1, U9.1, U12.2, U13.3, U13.PAD, U14.2, U16.C, U17.1, U17.3
NET_U1_25: R4.1, U1.25, U17.4
NET_U1_33: C17.1, C18.1, F1.1, U1.32, U1.33
NET_U1_71: C15.1, U1.71
NET_U1_106: C16.1, U1.106
NET_U1_136: R5.1, U1.136, U4.6
NET_U1_137: R6.1, U1.137, U4.5
NET_U1_138: R8.1, U1.138
NET_U1_142: U15.3, U15.4
NET_U1_143: R7.1, U1.143
NET_U2_3: R9.1, U2.3
NET_U2_7: R11.1, U2.7
NET_U3_1: R14.1, U3.1
NET_U3_2: R13.1, U3.2
NET_U3_18: U3.18, U3.19
NET_U5_6: R23.2, U5.6
NET_U5_8: R24.1, U5.8
NET_U6_2: R23.2, U5.6, U6.2
NET_U6_3: R23.1, U5.7, U6.3
NET_U7_20: C34.1, C39.1, U7.20
NET_U8_2: C27.1, R26.1, U8.2
NET_U8_5: C26.1, R25.1, U8.5
NET_U9_5: C28.1, C29.1, R27.1, R28.1, U9.5
NET_U13_1: C43.1, U13.1
NET_U13_6: R30.2, R31.1, U13.6
NET_U13_8: R29.1, U13.8
NET_U14_1: R33.1, R34.1, U14.1
NET_U14_3: R35.2, R36.1, U14.3
NET_U14_4: R32.1, U14.4, U17.2
NET_U15_1: R2.1, U15.1, U15.2
PROC_CAN1_RX: U1.103, U5.4
PROC_CAN1_TX: U1.104, U5.1
PROC_I2S2_CK: U1.69, U7.7
PROC_I2S2_EXT_SD: U1.28, U7.10
PROC_I2S2_SD: U1.29, U7.8
PROC_I2S2_WS: U1.73, U7.9, U7.11
PROC_SDIO_CK: R12.1, U1.113, U3.8
PROC_SDIO_D0: R15.1, U1.98, U3.4
PROC_SDIO_D1: R16.1, U1.99, U3.3
PROC_SDIO_D2: R17.1, U1.111, U3.15
PROC_SDIO_D3: R18.1, U1.112, U3.14
PROC_SDIO_D4: R19.1, U1.139, U3.13
PROC_SDIO_D5: R20.1, U1.140, U3.11
PROC_SDIO_D6: R21.1, U1.96, U3.7
PROC_SDIO_D7: R22.1, U1.97, U3.5
PROC_SPI1_MISO: U1.42, U2.2
PROC_SPI1_MOSI: U1.43, U2.5
PROC_SPI1_NSS: R10.1, U1.40, U2.1
PROC_SPI1_SCK: U1.41, U2.6
VCC_S1_7V3: C44.1, C47.1, C48.1, J1.1, R29.2, U13.4
VCC_TIER1_3V3: C1.1, C2.1, C3.1, C4.1, C5.1, C6.1, C7.1, C8.1, C9.1, C10.1, C11.1, C12.1, C13.1, C14.1, C21.1, C22.1, C23.1, C24.1, C25.1, C30.1, C31.1, C32.1, C33.1, C35.1, C36.1, C37.1, C38.1, C42.1, C45.1, C46.1, C49.1, F1.2, R4.2, R5.2, R6.2, R7.2, R9.2, R10.2, R11.2, R12.2, R13.2, R14.2, R15.2, R16.2, R17.2, R18.2, R19.2, R20.2, R21.2, R22.2, R30.1, R32.2, R33.2, R35.1, U1.6, U1.17, U1.30, U1.39, U1.52, U1.62, U1.72, U1.84, U1.95, U1.108, U1.121, U1.131, U1.144, U2.8, U3.9, U4.7, U4.8, U5.3, U7.3, U7.5, U7.12, U7.18, U12.4, U13.5, U14.6, U17.5
